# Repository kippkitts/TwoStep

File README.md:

TwoStep
=======

<a href=http://kippkitts.com/collections/frontpage/products/twostep-stepper-controller-shield>

The TwoStep Controller is a stepper motor controller shield for the Arduino.  It uses two L6470 stepper drivers to drive two motors at 40V, 5A each.  Provided here are the Eagle files for the board.  You can find the TwoStep Controller at the [kippkitts store](http://kippkitts.com/collections/frontpage/products/twostep-stepper-controller-shield).

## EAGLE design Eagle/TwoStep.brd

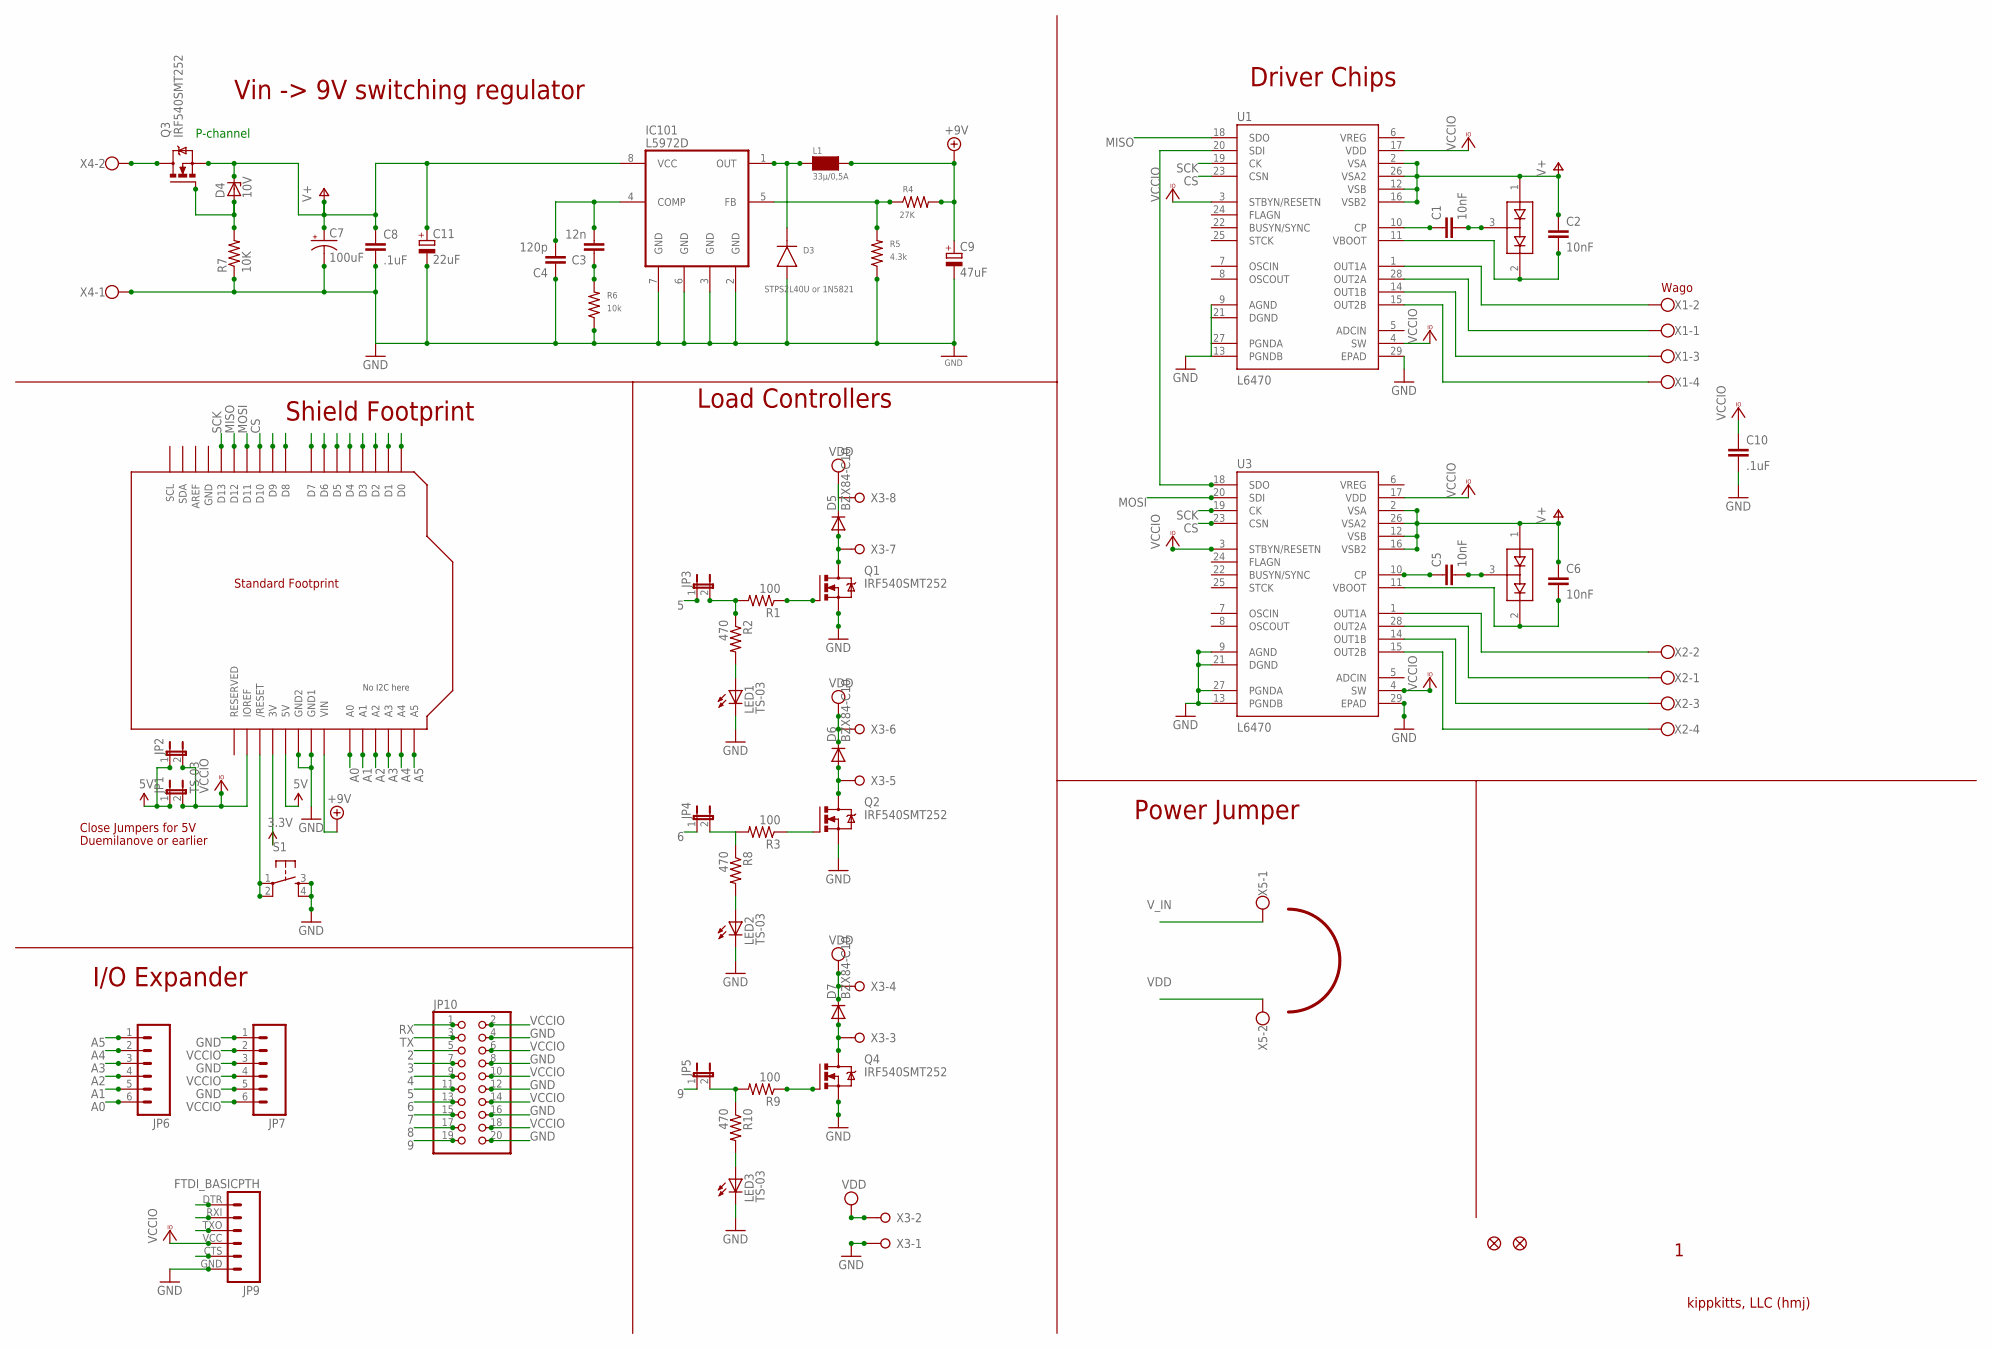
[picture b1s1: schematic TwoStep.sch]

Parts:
C1, C2, C5, C6: 10nF; 0603-CAP
C3: 12n; 0603-CAP
C4: 120p; 0603-CAP
C7: 100uF; NIPPON_F80
C8, C10: .1uF; 0603-CAP
C9: 47uF; PANASONIC_C
C11: 22uF; PANASONIC_C
D1, D2: BAV99; MISCELLANY_SOT23
D3: STPS2L40U or 1N5821; DO-214AA(SMB)
D4: 10V; SOT23
D5, D6, D7: BZX84-C10; SMA-DIODE_ALT
IC101: L5972D; SO-8
JP1: TS-03; 1X02
JP2: JUMPER-2SMD-NO; SJ_2S-NO
JP3, JP4, JP5: JUMPER-2SMD-NC; SJ_2S
JP6, JP7: M06SIP; 1X06
JP8, JP11: FIDUCIAL1X2; FIDUCIAL-1X2
JP9: FTDI_BASICPTH; FTDI_BASIC
JP10: PINHD-2X10HAND; 2X10HAND
L1: 33µ/0,5A; WE-PD-S
LED1, LED2, LED3: TS-03; CHIP-LED0603
Q1, Q2, Q3, Q4: IRF540SMT252; D-PAK_TO252AA
R1, R3, R9: 100; 0603-RES
R2, R8, R10: 470; 0603-RES
R4: 27K; 0603-RES
R5: 4.3k; 0603-RES
R6: 10k; 0603-RES
R7: 10K; 0603-RES
S1: TAC_SWITCHSMD; TACTILE_SWITCH_SMD
U1, U3: L6470; MISCELLANY_HTSSOP28
U2: ARDUINOR3-BPLACE
X1, X2: W237-4
X3: W237-08P; W237-8P
X4: W237-102
X5: W237-102; MPN 237-102

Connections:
1_OUT1A: U1.1 (OUT1A), X1.2
1_OUT1B: U1.14 (OUT1B), X1.3
1_OUT2A: U1.28 (OUT2A), X1.1
1_OUT2B: U1.15 (OUT2B), X1.4
2: JP10.5, U2.D2
2_OUT1A: U3.1 (OUT1A), X2.2
2_OUT1B: U3.14 (OUT1B), X2.3
2_OUT2A: U3.28 (OUT2A), X2.1
2_OUT2B: U3.15 (OUT2B), X2.4
3: JP10.7, U2.D3
3.3V: U2.3V
4: JP10.9, U2.D4
5: JP3.1, JP10.11, U2.D5
5V: JP1.1, JP2.1, U2.5V
6: JP4.1, JP10.13, U2.D6
7: JP10.15, U2.D7
8: JP10.17, U2.D8
9: JP5.1, JP10.19, U2.D9
+9V: C9.+, L1.2 (4), R4.2, U2.VIN
A0: JP6.6, U2.A0
A1: JP6.5, U2.A1
A2: JP6.4, U2.A2
A3: JP6.3, U2.A3
A4: JP6.2, U2.A4
A5: JP6.1, U2.A5
CS: U1.23 (CSN), U2.D10, U3.23 (CSN)
CTS: JP9.CTS (5)
DTR: JP9.DTR (1)
GND: C4.1, C7.-, C8.2, C9.-, C10.2, C11.-, D3.A, IC101.2 (GND), IC101.3 (GND), IC101.6 (GND), IC101.7 (GND), JP7.1, JP7.3, JP7.5, JP9.GND (6), JP10.4, JP10.8, JP10.12, JP10.16, JP10.20, LED1.C, LED2.C, LED3.C, Q1.3 (S), Q2.3 (S), Q4.3 (S), R5.1, R6.1, R7.1, S1.3, S1.4, U1.9 (AGND), U1.13 (PGNDB), U1.21 (DGND), U1.27 (PGNDA), U1.29 (EPAD), U2.GND, U2.GND1, U2.GND2, U3.9 (AGND), U3.13 (PGNDB), U3.21 (DGND), U3.27 (PGNDA), U3.29 (EPAD), X3.1, X4.1
MISO: U1.18 (SDO), U2.D12
MOSI: U2.D11, U3.20 (SDI)
unnamed: Q1.1 (G), R1.1
unnamed: JP3.2, R1.2, R2.1
unnamed: Q2.1 (G), R3.1
unnamed: LED1.A, R2.2
unnamed: D4.1 (A), Q3.1 (G), R7.2
unnamed: LED2.A, R8.2
unnamed: C1.1, U1.10 (CP)
unnamed: C1.2, D1.3 (COM)
unnamed: C2.2, D1.2 (C2), U1.11 (VBOOT)
unnamed: U1.20 (SDI), U3.18 (SDO)
unnamed: JP4.2, R3.2, R8.1
unnamed: Q4.1 (G), R9.1
unnamed: LED3.A, R10.2
unnamed: C5.1, U3.10 (CP)
unnamed: C5.2, D2.3 (COM)
unnamed: C6.2, D2.2 (C2), U3.11 (VBOOT)
unnamed: JP5.2, R9.2, R10.1
unnamed: D5.A, Q1.4 (D), X3.7
unnamed: S1.1, S1.2, U2.RESET (/RESET)
unnamed: D6.A, Q2.4 (D), X3.5
unnamed: D7.A, Q4.4 (D), X3.3
unnamed: D3.C (K), IC101.1 (OUT), L1.1 (3)
unnamed: IC101.5 (FB), R4.1, R5.2
unnamed: C3.2, C4.2, IC101.4 (COMP)
unnamed: C3.1, R6.2
RX: JP9.RXI (2), JP10.1, U2.D0
SCK: U1.19 (CK), U2.D13, U3.19 (CK)
TX: JP9.TXO (3), JP10.3, U2.D1
V+: C2.1, C6.1, C7.+, C8.1, C11.+, D1.1 (A1), D2.1 (A1), D4.3 (C), IC101.8 (VCC), Q3.3 (S), U1.2 (VSA), U1.12 (VSB), U1.16 (VSB2), U1.26 (VSA2), U3.2 (VSA), U3.12 (VSB), U3.16 (VSB2), U3.26 (VSA2)
VCCIO: C10.1, JP1.2, JP2.2, JP7.2, JP7.4, JP7.6, JP9.VCC (4), JP10.2, JP10.6, JP10.10, JP10.14, JP10.18, U1.3 (STBYN/RESETN), U1.4 (SW), U1.17 (VDD), U2.IOREF, U3.3 (STBYN/RESETN), U3.4 (SW), U3.17 (VDD)
VDD: D5.C, D6.C, D7.C, X3.2, X3.4, X3.6, X3.8, X5.2
V_IN: Q3.4 (D), X4.2, X5.1

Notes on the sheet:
Wago
kippkitts, LLC (hmj)
Driver Chips
Vin -> 9V switching regulator
Shield Footprint
Close Jumpers for 5V
Duemilanove or earlier
P-channel
Load Controllers
I/O Expander
Power Jumper

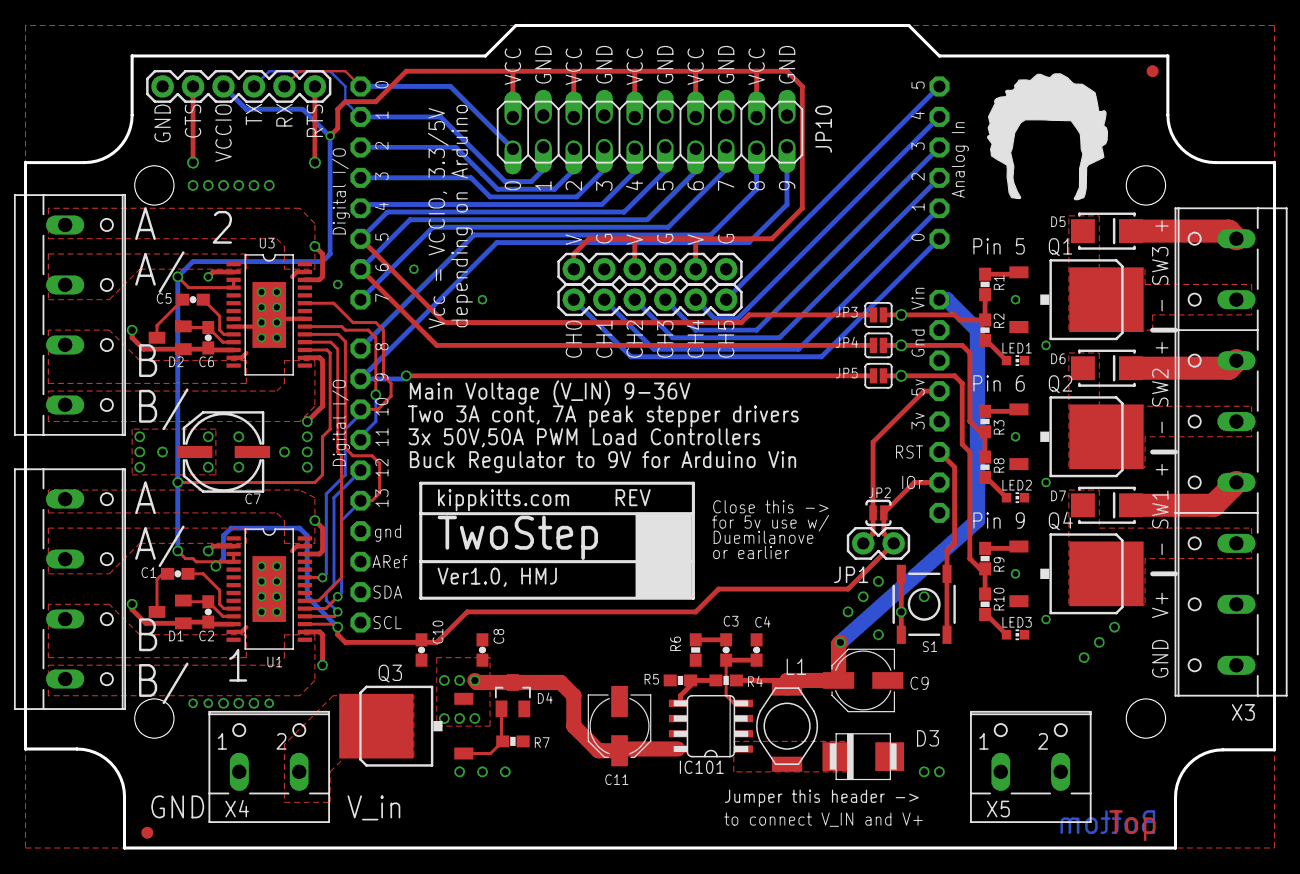
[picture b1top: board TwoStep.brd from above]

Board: 2 copper layers, 104.1 x 68.6 mm, 58 parts (0 on the bottom side), 60 nets.

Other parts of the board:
KK_LOGO: TOP_DOCU_10MM

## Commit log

2014-03-11 Add Eagle Files

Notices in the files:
parts and their libraries:
SparkFun: Licensing: CC v3.0 Share-Alike You are welcome to use this library for commercial purposes.
